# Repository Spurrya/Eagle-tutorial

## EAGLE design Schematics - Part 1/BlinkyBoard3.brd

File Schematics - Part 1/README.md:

# PCB Design Workshop

Components used:

1. (Battery) CR1220 -> CR1220-SMD

2. (Timer) 555 -> LM555D

3. (Capacitors) C-US -> C0805 (x2)

4. (Resistors) R-US -> R0805 (x4)

5. (LEDs) LED -> CHIPLED_0805 (x2)

Step 1: Download Eagle

  - Link: http://www.cadsoftusa.com/download-eagle/ 
  
Step 2: Install Adafruit Library

  - Link: https://github.com/adafruit/Adafruit-Eagle-Library 
  
  - Copy and paste the .lbr file into C: -> Program Files -> Eagle -> lbr
  
Step 3: Enable Eagle to use Adafruit Library

  - In Eagle, left click library -> use all
  
Step 4: Create new Project

  - Left click projects -> choose new project, left click you project -> choose new schematic
  
Step 5: Add components

  - See list of components above
  
Step 6: Connect components

Step 7: Clean up

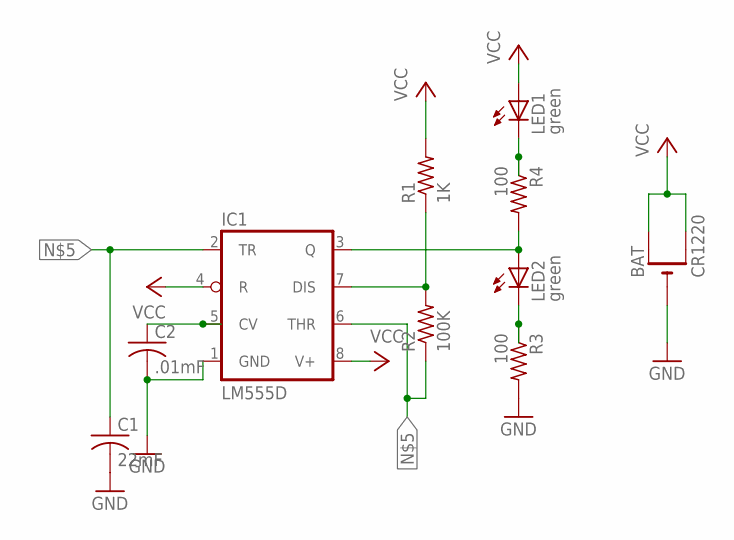
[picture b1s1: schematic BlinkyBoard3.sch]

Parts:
BAT: CR1220; CR1220-SMD
C1: 22mF; C0805
C2: .01mF; C0805
IC1: LM555D; SO08
LED1, LED2: green; CHIPLED_0805
R1: 1K; R0805
R2: 100K; R0805
R3, R4: 100; R0805

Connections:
GND: BAT.-, C1.2, C2.2, IC1.1 (GND), R3.2
unnamed: LED1.C, R4.1
unnamed: IC1.3 (Q), LED2.A, R4.2
unnamed: LED2.C, R3.1
unnamed: IC1.7 (DIS), R1.1, R2.2
unnamed: C1.1, IC1.2 (TR), IC1.6 (THR), R2.1
unnamed: C2.1, IC1.5 (CV)
VCC: BAT.+$1 (+), BAT.+$2 (+1), IC1.4 (R), IC1.8 (V+), LED1.A, R1.2

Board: 2 copper layers, 10 parts (0 on the bottom side), 8 nets, no tracks yet.

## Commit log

2016-05-16 Added schematics
2016-05-16 Added PCB design folder
2016-05-16 A minor change in the title
2016-05-17 updated the schematics
2016-05-17 Updated the PCB board
2016-05-17 Added components onto PCB
2016-05-17 Added versions of completness of the board design
2016-05-18 Updated PCB Design part 2
2016-05-18 Removed few files
2016-05-18 Remaned files so they appear numerically
2016-05-18 Update README.md
    added read me
2016-05-18 Adding bullet points
2016-05-18 Update README.md
    added steps
2016-05-18 Added more stuff to readme
2016-05-18 readmeeee
2016-05-18 added an image
